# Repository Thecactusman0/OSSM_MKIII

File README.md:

# OSSM_MKIII
The Open Source Singularitron Mini is a small and condensed version of Zack Freedman's Singularitron smartwatch.

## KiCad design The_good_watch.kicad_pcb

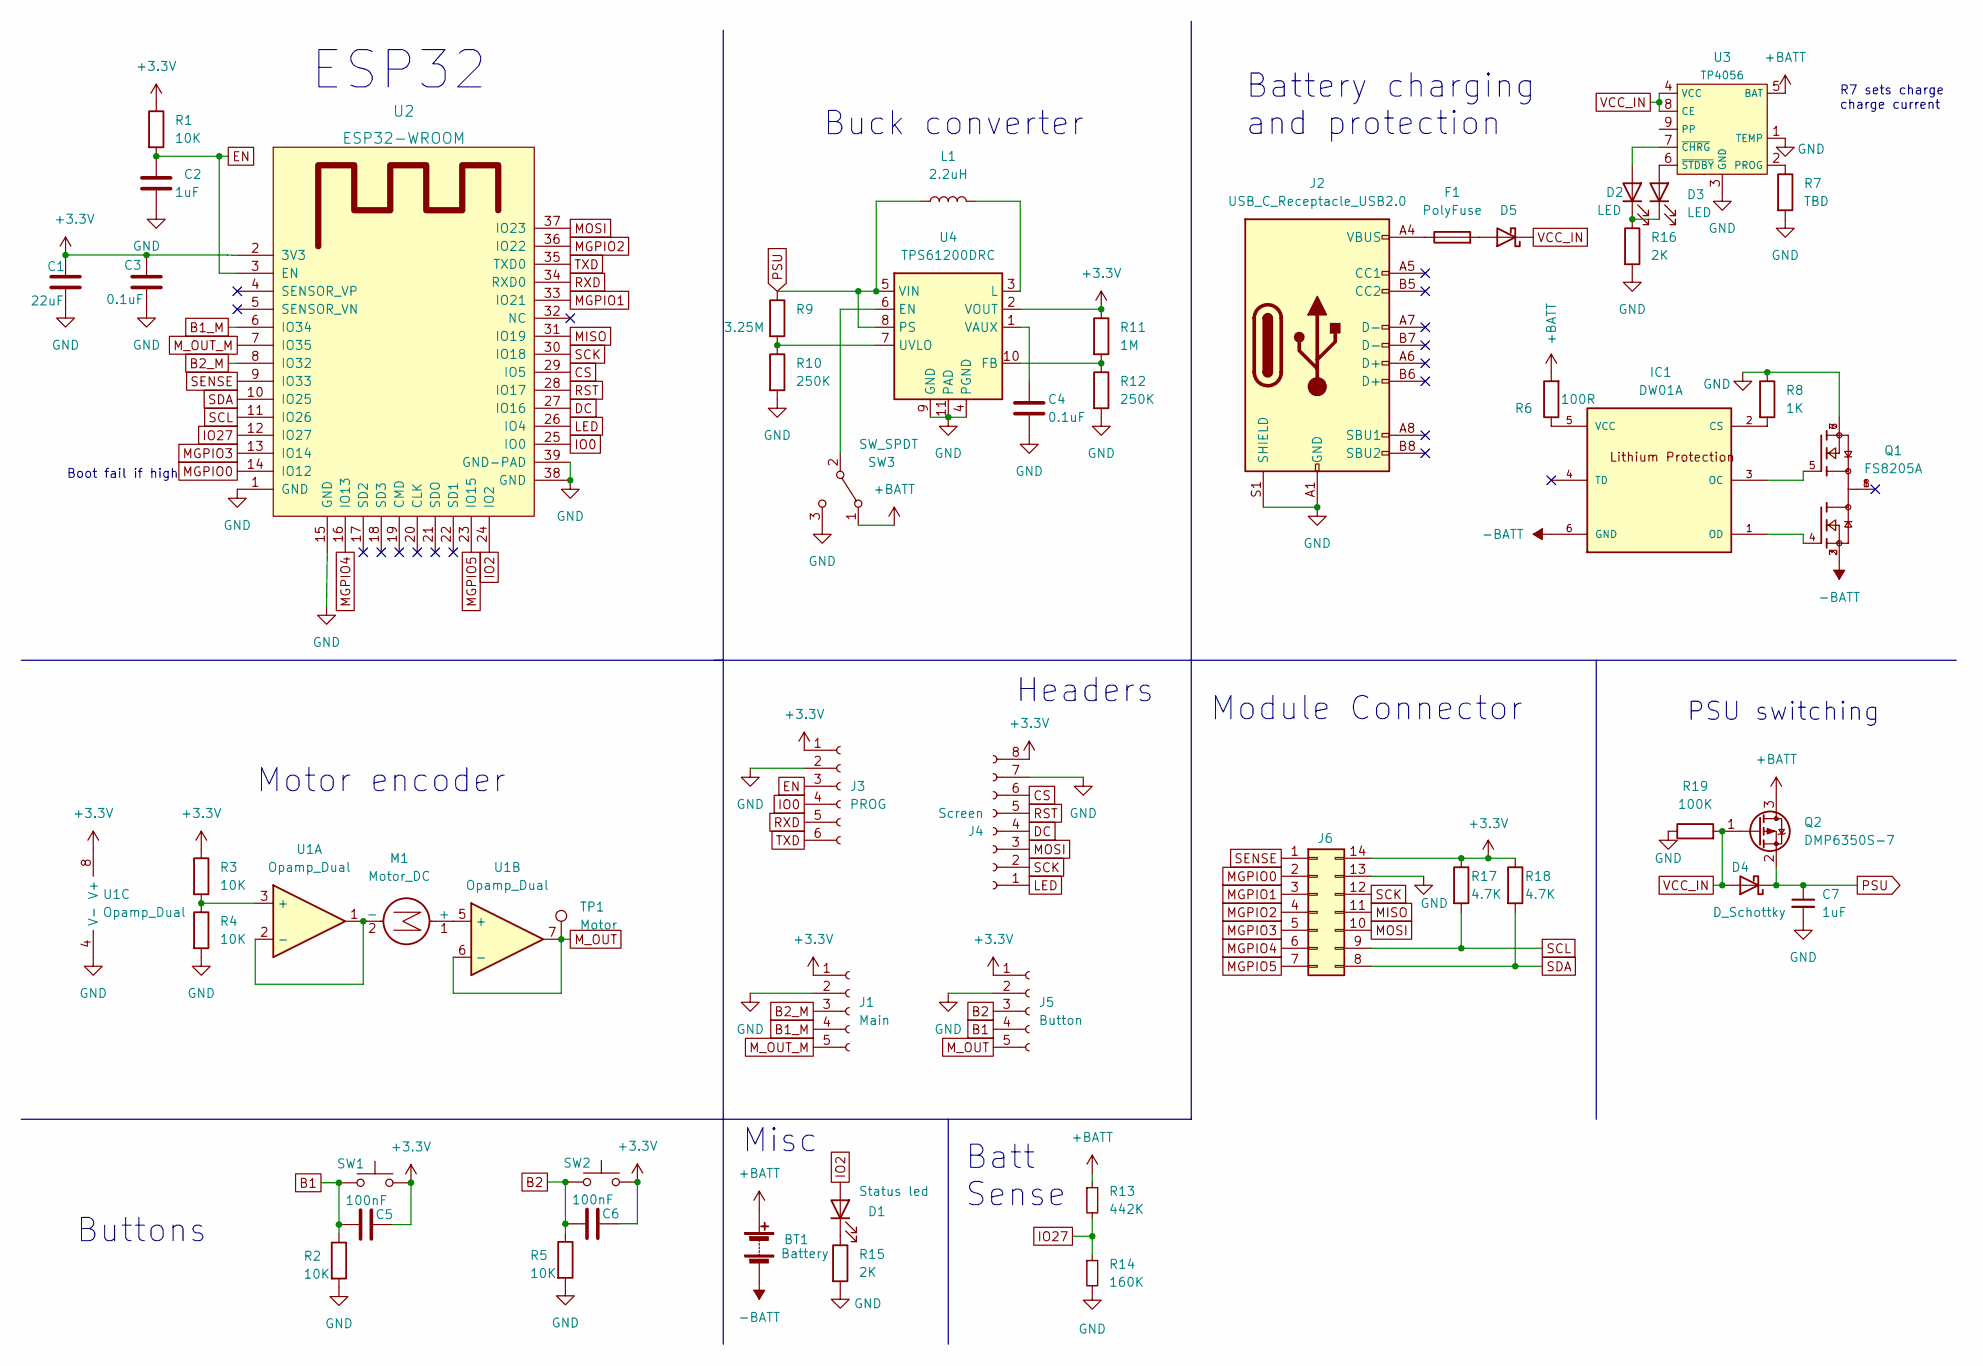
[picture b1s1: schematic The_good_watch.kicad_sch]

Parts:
BT1: Battery; PinHeader_2x01_P2.00mm_Vertical
C1: 22uF; C_0805_2012Metric_Pad1.18x1.45mm_HandSolder
C2, C7: 1uF; C_0805_2012Metric_Pad1.18x1.45mm_HandSolder
C3, C4: 0.1uF; C_0805_2012Metric_Pad1.18x1.45mm_HandSolder
C5, C6: 100nF; C_0805_2012Metric_Pad1.18x1.45mm_HandSolder
D1: Status led; LED_0603_1608Metric_Pad1.05x0.95mm_HandSolder
D2, D3: LED; LED_0603_1608Metric_Pad1.05x0.95mm_HandSolder
D4, D5: D_Schottky; D_0603_1608Metric
F1: PolyFuse; Fuse_0603_1608Metric
IC1: DW01A; SOT23-6; MPN DW01A; LCSC C351410
J1: Main; PinHeader_1x05_P2.54mm_Vertical
J2: USB_C_Receptacle_USB2.0; USB_C_Receptacle_GCT_USB4085
J3: PROG; PinSocket_1x06_P2.54mm_Vertical
J4: Screen; PinSocket_1x08_P2.54mm_Vertical
J5: Button; PinHeader_1x05_P2.54mm_Vertical
J6: Conn_02x07_Counter_Clockwise; PinHeader_2x07_P1.27mm_Horizontal
L1: 2.2uH; L_1008_2520Metric_Pad1.43x2.20mm_HandSolder
M1: Motor_DC; PinSocket_1x02_P2.54mm_Vertical
Q1: FS8205A; SOP65P640X120-8N; PARTREV 1.7
Q2: DMP6350S-7; SOT-23
R1, R2, R3, R4, R5: 10K; R_0805_2012Metric_Pad1.20x1.40mm_HandSolder
R6: 100R; R_0805_2012Metric
R7: TBD; R_0805_2012Metric
R8: 1K; R_0805_2012Metric
R9: 3.25M; L_0805_2012Metric
R10, R12: 250K; L_0805_2012Metric
R11: 1M; L_0805_2012Metric
R13: 442K; R_0402_1005Metric_Pad0.72x0.64mm_HandSolder
R14: 160K; R_0402_1005Metric_Pad0.72x0.64mm_HandSolder
R15, R16: 2K; R_0805_2012Metric
R17, R18: 4.7K; R_0805_2012Metric
R19: 100K; R_0805_2012Metric
SW1: SW_Push; SW_Push_1P1T-MP_NO_Horizontal_Alps_SKRTLAE010
SW2: SW_Push; SW_PUSH_6mm
SW3: SW_SPDT; SW_SPDT_CK-JS102011SAQN
TP1: Motor; TestPoint_Pad_D2.0mm
U1: Opamp_Dual; SOIC-8_3.9x4.9mm_P1.27mm
U2: ESP32-WROOM
U3: TP4056; SOIC-8-1EP_3.9x4.9mm_P1.27mm_EP2.29x3mm
U4: TPS61200DRC; Texas_S-PVSON-N10_ThermalVias

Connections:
+3V3: C1.1, C3.1, C5.2, C6.2, J1.1, J3.1, J4.8, J5.1, J6.14, R1.1, R3.1, R11.1, R17.1, R18.1, SW1.2, SW2.2, U1.8 (V+), U2.2 (3V3), U4.2 (VOUT)
+BATT: BT1.1 (+), Q2.3 (D), R6.2, R13.1, SW3.1 (A), U3.5 (BAT)
-BATT: BT1.2 (-), IC1.6 (GND), Q1.2, Q1.3
B1: C5.1, J5.4, R2.1, SW1.1
B1_M: J1.4, U2.6 (IO34)
B2: C6.1, J5.3, R5.1, SW2.1
B2_M: J1.3, U2.8 (IO32)
CS: J4.6, U2.29 (IO5)
DC: J4.4, U2.27 (IO16)
EN: C2.1, J3.3, R1.2, U2.3 (EN)
GND: C1.2, C2.2, C3.2, C4.2, C7.2, J1.2, J2.A1 (GND), J2.A12 (GND), J2.B1 (GND), J2.B12 (GND), J2.S1 (SHIELD), J3.2, J4.7, J5.2, J6.13, Q1.6, Q1.7, R2.2, R4.2, R5.2, R7.2, R8.1, R10.2, R12.2, R14.2, R15.2, R16.2, R19.1, SW3.3 (C), U1.4 (V-), U2.1 (GND), U2.15 (GND), U2.38 (GND), U2.39 (GND-PAD), U3.1 (TEMP), U3.3 (GND), U4.4 (PGND), U4.9 (GND), U4.11 (PAD)
IO0: J3.4, U2.25 (IO0)
IO2: D1.2 (A), U2.24 (IO2)
IO27: R13.2, R14.1, U2.12 (IO27)
LED: J4.1, U2.26 (IO4)
MGPIO0: J6.2, U2.14 (IO12)
MGPIO1: J6.3, U2.33 (IO21)
MGPIO2: J6.4, U2.36 (IO22)
MGPIO3: J6.5, U2.13 (IO14)
MGPIO4: J6.6, U2.16 (IO13)
MGPIO5: J6.7, U2.23 (IO15)
MISO: J6.11, U2.31 (IO19)
MOSI: J4.3, J6.10, U2.37 (IO23)
M_OUT: J5.5, TP1.1, U1.6 (-), U1.7
M_OUT_M: J1.5, U2.7 (IO35)
unnamed: C4.1, U4.1 (VAUX)
unnamed: D1.1 (K), R15.1
unnamed: D2.1 (K), D3.1 (K), R16.1
unnamed: D2.2 (A), U3.7 (~CHRG)
unnamed: D3.2 (A), U3.6 (~STDBY)
unnamed: D5.2 (A), F1.2
unnamed: F1.1, J2.A4 (VBUS), J2.A9 (VBUS), J2.B4 (VBUS), J2.B9 (VBUS)
unnamed: IC1.1 (OD), Q1.4
unnamed: IC1.2 (CS), R8.2
unnamed: IC1.3 (OC), Q1.5
unnamed: IC1.5 (VCC), R6.1
unnamed: L1.2, U4.3 (L)
unnamed: M1.1 (+), U1.5 (+)
unnamed: M1.2 (-), U1.1, U1.2 (-)
unnamed: R3.2, R4.1, U1.3 (+)
unnamed: R7.1, U3.2 (PROG)
unnamed: R9.2, R10.1, U4.7 (UVLO)
unnamed: R11.2, R12.1, U4.10 (FB)
unnamed: SW3.2 (B), U4.6 (EN)
PSU: C7.1, D4.1 (K), L1.1, Q2.2 (S), R9.1, U4.5 (VIN), U4.8 (PS)
RST: J4.5, U2.28 (IO17)
RXD: J3.5, U2.34 (RXD0)
SCK: J4.2, J6.12, U2.30 (IO18)
SCL: J6.9, R17.2, U2.11 (IO26)
SDA: J6.8, R18.2, U2.10 (IO25)
SENSE: J6.1, U2.9 (IO33)
TXD: J3.6, U2.35 (TXD0)
VCC_IN: D4.2 (A), D5.1 (K), Q2.1 (G), R19.2, U3.4 (VCC), U3.8 (CE)

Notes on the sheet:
ESP32
Buttons
Battery charging and protection
Buck converter
Module Connector
PSU switching
Batt Sense
Headers
Misc
Boot fail if high
R7 sets charge charge current
Motor encoder

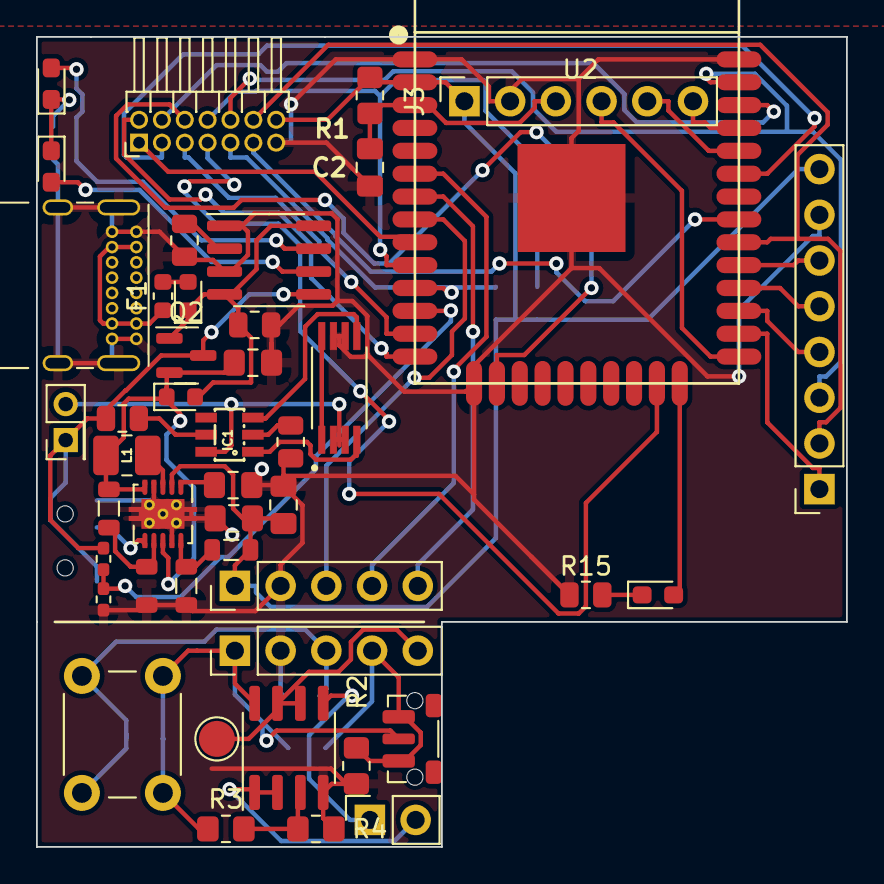
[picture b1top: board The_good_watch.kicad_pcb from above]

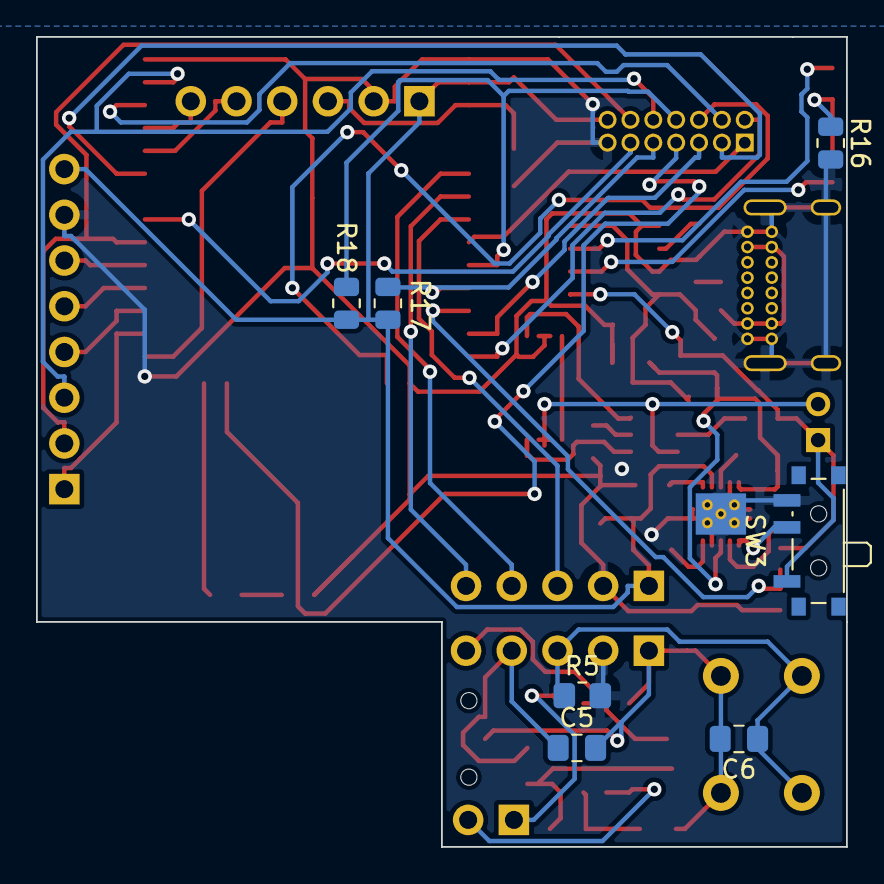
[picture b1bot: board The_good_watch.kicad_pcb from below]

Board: 2 copper layers, 45.0 x 45.0 mm, 52 parts (7 on the bottom side), 53 nets.

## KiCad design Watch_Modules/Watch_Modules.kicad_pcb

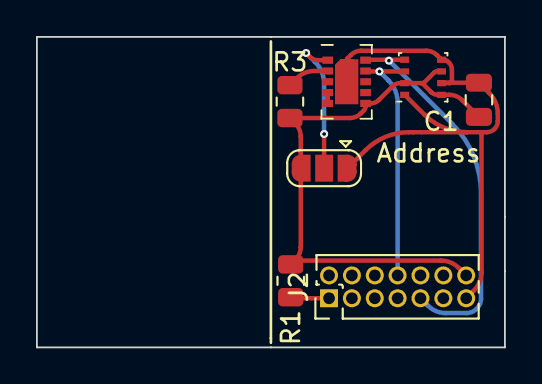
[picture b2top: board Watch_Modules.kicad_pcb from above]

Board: 2 copper layers, 26.0 x 17.2 mm, 7 parts (0 on the bottom side), 8 nets.

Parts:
Address: SolderJumper_3_Open; SolderJumper-3_P1.3mm_Open_RoundedPad1.0x1.5mm
C1: 100nF; C_0805_2012Metric
J2: Conn_02x07_Counter_Clockwise; PinHeader_2x07_P1.27mm_Vertical
R1: NC; R_0805_2012Metric
R3: 4.7K; R_0805_2012Metric
U1: BME280; Bosch_LGA-8_2.5x2.5mm_P0.65mm_ClockwisePinNumbering
U2: CCS811; AMS_LGA-10-1EP_2.7x4mm_P0.6mm

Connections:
unnamed: Address.1 (A), C1.2, J2.13, U1.1 (GND), U1.5 (SDO), U1.7 (GND), U2.11 (GND)
unnamed: Address.2 (C), U2.1 (ADDR)
unnamed: Address.3 (B), C1.1, J2.14, R1.2, R3.1, U1.2 (CSB), U1.6 (VDDIO), U1.8 (VDD), U2.6 (VDD)
unnamed: J2.1, R1.1
unnamed: R3.2, U2.2 (~RESET)
unnamed: J2.8, U1.3 (SDI), U2.9 (SDA)
unnamed: J2.9, U1.4 (SCK), U2.10 (SCL)
unnamed: U2.4 (PWM), U2.5 (Sense)

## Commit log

2022-06-06 Main parts added and trial routing
    Added esp32 module and components, power, lipo management and inputs
2022-06-07 Added battery sense and regulator shutoff
2022-06-08 Connector layout trial
2022-06-10 Finished layout and routing
    Only minor graphical cleanup remains
2022-06-11 Added watch module footprint
2022-06-11 Added blank module pcb file
2022-06-11 Added copper fill
2022-06-11 Set theme jekyll-theme-cayman
2022-06-11 Added graphics
2022-06-12 Organization changes
2022-06-15 Changed spring connector for modules to pinheaders.
    still need to update modules
2022-06-22 Graphical fixes, minor electrical fixes and enviro sensor module trial
    Fixed some component values and added i2c pullups
2022-06-24 Added power switching
    Uses usb power when plugged in and disconnects battery.
2022-06-24 Added charge current lookup table
2022-06-26 Fixed connector problems
2022-06-26 Fixed more connector problems
2022-06-28 Fixed analog pins
    encoder pins shut down when wifi enabled now fixed
2022-06-28 Added schottky diode for reverse voltage protection
2022-06-28 Added diode protection on usb pwr in and redid layout
2022-06-29 Layout changes and fuse
    Added fuse and fixed mosfet. Not changed on the pcb
2022-07-02 Changed power switch
2022-07-02 Pcb routed
